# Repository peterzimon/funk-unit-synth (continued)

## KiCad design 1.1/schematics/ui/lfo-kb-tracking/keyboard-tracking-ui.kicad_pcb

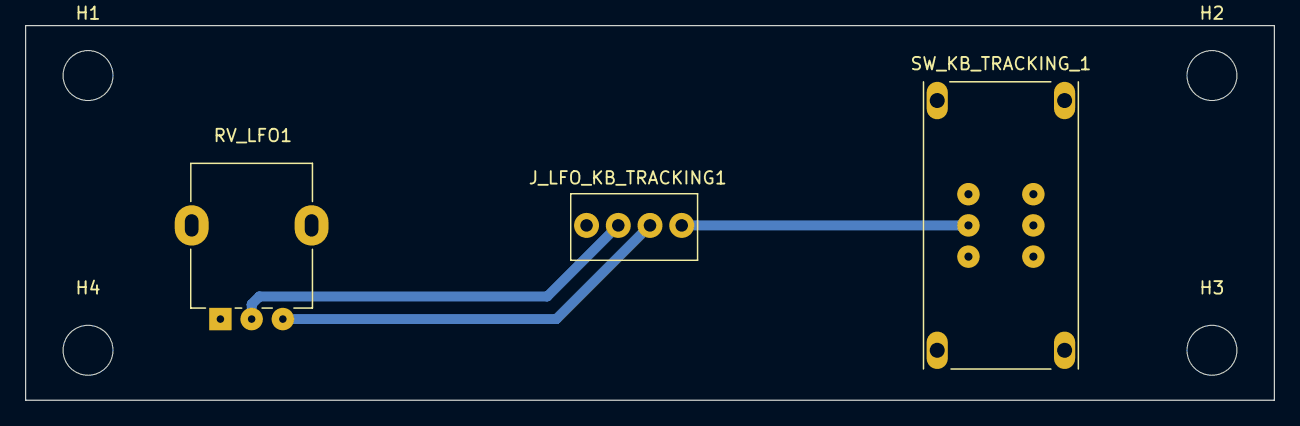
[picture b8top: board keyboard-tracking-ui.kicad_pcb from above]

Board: 2 copper layers, 100.0 x 30.0 mm, 7 parts (0 on the bottom side), 4 nets.

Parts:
H1, H2, H3, H4: MountingHole; MountingHole_4mm
J_LFO_KB_TRACKING1: Conn_01x04; NSL25_01x04_Vertical
RV_LFO1: 100k; Potentiometer_Alpha_RD901F-40-00D_Single_Vertical
SW_KB_TRACKING_1: SW_DPDT_x2; DPDT Korg Style Switch

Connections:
GND: J_LFO_KB_TRACKING1.4, RV_LFO1.1, SW_KB_TRACKING_1.5 (C)
KB_TRACKING: J_LFO_KB_TRACKING1.1, SW_KB_TRACKING_1.3 (B)
LFO_IN: J_LFO_KB_TRACKING1.2, RV_LFO1.3
LFO_OUT: J_LFO_KB_TRACKING1.3, RV_LFO1.2

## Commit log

2023-05-06 Let the fuckery begin
2023-05-06 Added schematics for minimal version
    This version distributes the played notes equally between the available voices.
2023-05-06 Cleanups
2023-05-07 Added pico-lib submodule to the project.
2023-05-07 Added fundamentals based on Borneborn
    - copied base classes
    - removed class attachments in favor of singletons
2023-05-07 Removed CV and gate related code
2023-05-07 Removed CV and gate
2023-05-09 Added time based paraphonic converter
2023-05-09 Added DCO logic incl. PIOs
2023-05-09 Cleanup
2023-05-09 Fixed div by 0 bug
2023-05-10 Updated DCO pins
2023-05-10 Updated paraphonic logic
    The original idea was _almost_ good. The only change it needed is to
    reset _all the voices_ to the same note on every "first" key press, ie.
    once all the keys are released and then a new key is pressed. After this
    distrubute the notes evenly just like before.
2023-05-11 Updated paraphonic mode
    Added a setting parameter for voice stacking for paraphonic mode. It
    allows choosing between distributing all voices amongst the voices vs
    just playing as many notes as held.
2023-05-12 Added monophonic mode
2023-05-12 Updated synth mode setting
2023-05-14 Fixed a mono bug and tested DCO resets (works)
2023-05-22 Minor updates
2023-05-26 Updated DCO
2023-05-27 Updated f=0 amplitude compensation
    Until now if the frequency of a given voice was f=0Hz then I've set both
    the DCO freq. and the amplitude compensation to zero. This however
    resulted a negative DC offset on the output of the DCO. Instead if I set
    _only_ the amplitude to zero (and use another voice's frequency to
    reset the given DCO) then the DC output is closer to 0 which helps
    minimising the pop when voices are turned on.
2023-05-27 DCO schematic update
    Changed the DCO design from using a PNP transistor for the switch,
    positive charge and an inverting amp with bias for the saw output. This
    allows to bias the sawtooth output to oscillate around 0V which makes
    possible to set precise pulse width values for all voices regardless of
    potential component differences. Also, this eventually needs less
    component altogether.
2023-05-27 Added a couple of test points
2023-05-27 DCO schematic cleanup
2023-05-28 Added solo submode
    ATM the plan is to have only a single VCA and ADSR which brings up the
    question of how to handle paraphonic mode. The question is what to do
    with the notes which are released on the keyboard and how that would
    work with the envelope.
    The core idea is that voice #1 will control the envelope, ie. when a new
    note is played on voice #1 that'll trigger a new gate out. When more
2023-05-28 Refined solo mode
2023-05-28 Added pulse width mod schematics
2023-05-29 Updated PWM values
2023-06-03 Added digital ADSR (untested)
2023-06-04 Updated ADSR logic and added license
2023-06-04 Updated ADSR code and DAC schem.
2023-06-04 Added ADSR states based on UI input
2023-06-04 Setting ADSR values
2023-06-11 Updated VCA
2023-06-11 Coded portamento (untested)
2023-06-11 Added keyboard tracking DAC (untested)
2023-06-11 Updated kb tracking for analog switch
2023-06-11 Added all UI components to schematics
    - digital UI
    - filter UI
    - updated voice interface connection
    - simplified schematics a lot
2023-06-11 Basic mono & para modes tested and working
2023-06-11 PARA mode cleanup
2023-06-11 Basic FAT mode working
2023-06-11 Working portamento
2023-06-11 Added portamento to fat mono mode
2023-06-11 Added detune to FAT mono mode... BADASS
2023-06-11 Refined KB tracking output
2023-06-11 Implemented velocity filter mod
2023-06-11 Refined voice values
2023-06-18 Added switch MUX (untested)
2023-06-18 Updated MUX reading
    For some reason I couldn't figure out yet, there was one step offset
    in the reading of the multiplexer input. :/ Now it works as intended
    but it's still annoying.
2023-06-18 Added mode switch
2023-06-18 Added variable long release
2023-06-18 Added pitch bend to MONO + UNISON
2023-06-18 Added pitch bend to paraphonic mode
2023-06-18 Applied ring time to decay values
2023-06-20 Added panel design 1.0
2023-06-20 Schemo work
2023-06-24 Simplified PWM switch IO
2023-06-25 Updated schem. + added JLCPCB gerbers
2023-07-02 Panel graphics update
2023-07-09 1.0 bugfixes
2023-07-09 Added 1.1
2023-07-09 Updated 1.1 mixer level
2023-07-10 ✨ 1.1 Release
    Hardware
    - Fixes missing capacitor on the inputs of mixers. At f=0Hz the DCO's produce a DC output which shifts the center point of DCO's where f>0Hz. This happens on both the sawtooth and the squarewave outp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
    - Decreases the aplification of mixers. The sum of 6 voices on both saw and square mixers are way too strong and hit the op-amp limits (+/-12V). The first stage of the mixers are reduced now to 1/3 o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
    Software
    - Updates the MUX and the amp compensation output pin numbers according to the schematics.
2023-07-10 Readme update
2023-07-10 Remove .vscode
2023-07-10 Added changelog to 1.0
2023-07-10 Added changelog to v1.1
2023-07-10 Added pico-lib as a submodule to 1.0
2023-07-10 Added pico-lib as a submodule to 1.1
2023-08-12 Updates to 1.0
2023-08-12 1.1 changes
2023-08-13 Digital filter mod updates
    - added fixed modwheel control
    - fixed velocity and keyboard tracking bug
2023-08-13 Copied 1.0 code to 1.1
2023-08-18 Bugfixes
2023-08-18 Added SMD voice
2023-08-31 Removed a bunch of unnecessary backups
2023-09-08 Copy code 1.0 to 1.1
2023-09-08 pico lib changes
2023-09-09 Using kicad-libs submodule in 1.1
2023-09-09 Updated footprint links
2023-09-09 Fixed ADC channel number bug
2023-09-09 Added sound source UI
2023-09-10 Added envelope UI connections
2023-09-10 Added envelope UI
2023-09-10 Made sound source UI PCB narrower
2023-09-10 Made envelope UI narrower
2023-09-10 Envelope UI refinements
2023-09-11 Updated envelope UI and filter
2023-09-16 Added UI PCB's
2023-09-16 Added chord logic (untested)
2023-09-16 Updated saving history
2023-09-16 Kinda working chord machine
2023-09-16 Chord fixes
2023-09-17 Chordify working
2023-09-17 UI response time optimisiation
2023-12-26 Added UI PCB design
2023-12-26 Added panel design
2023-12-26 Added ENABLE_CHORD_MEMORY constant
    Chord logic was added so that Flame's version can also play chords.
    However, this firmware may be used with versions that don't have the
    chord memory feature so to save CPU time it's now possible to turn off
    the feature globally.
2023-12-27 Added MIDI channel (fixed to CH5) condition
